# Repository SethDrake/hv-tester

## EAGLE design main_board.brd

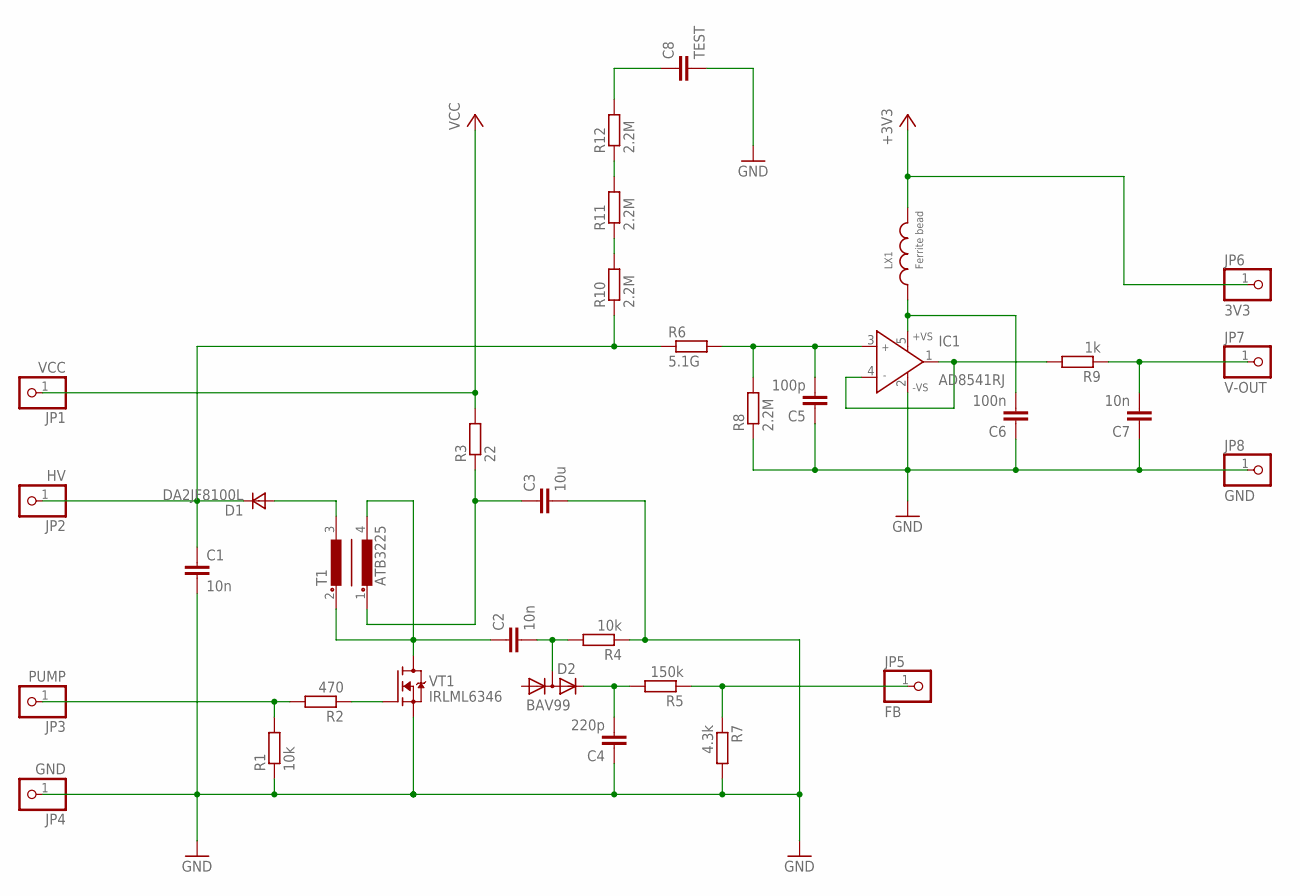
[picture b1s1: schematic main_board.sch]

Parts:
C1: 10n; C1206
C2, C7: 10n; C0805
C3: 10u; C0805
C4: 220p; C0805
C5: 100p; C0805
C6: 100n; C0805
C8: TEST; C1206
D1: DA2JF8100L; SOD323
D2: BAV99; SOT23
IC1: AD8541RJ; SOT23-5
JP1: VCC; 1X01
JP2: HV; 1X01
JP3: PUMP; 1X01
JP4, JP8: GND; 1X01
JP5: FB; 1X01
JP6: 3V3; 1X01
JP7: V-OUT; 1X01
LX1: Ferrite bead; WE-KI_0805A
R1, R4: 10k; M0805
R2: 470; M0805
R3: 22; M0805
R5: 150k; M0805
R6: 5.1G; P0817/22
R7: 4.3k; M0805
R8, R10, R11, R12: 2.2M; M0805
R9: 1k; M0805
T1: ATB3225
VT1: IRLML6346; SOT23

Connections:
+3V3: JP6.1, LX1.2
FB: JP5.1, R5.1, R7.1
GND: C1.2, C3.2, C4.1, C5.1, C6.1, C7.1, C8.2, IC1.2 (-VS), JP4.1, JP8.1, R1.1, R4.1, R7.2, R8.1, VT1.2 (S)
HV: C1.1, D1.1 (C), JP2.1, R6.1, R10.1
unnamed: D1.2 (A), T1.3
unnamed: C6.2, IC1.5 (+VS), LX1.1
unnamed: C2.1, T1.2, T1.4, VT1.3 (D)
unnamed: C3.1, R3.1, T1.1
unnamed: C2.2, D2.3 (K1A2), R4.2
unnamed: R10.2, R11.1
unnamed: R2.1, VT1.1 (G)
unnamed: R11.2, R12.1
unnamed: C4.2, D2.2 (K2), R5.2
unnamed: IC1.1 (OUT), IC1.4 (IN-), R9.2
unnamed: C5.2, IC1.3 (IN+), R6.2, R8.2
PUMP: JP3.1, R1.2, R2.2
TEST: C8.1, R12.2
V-OUT: C7.2, JP7.1, R9.1
VCC: JP1.1, R3.2

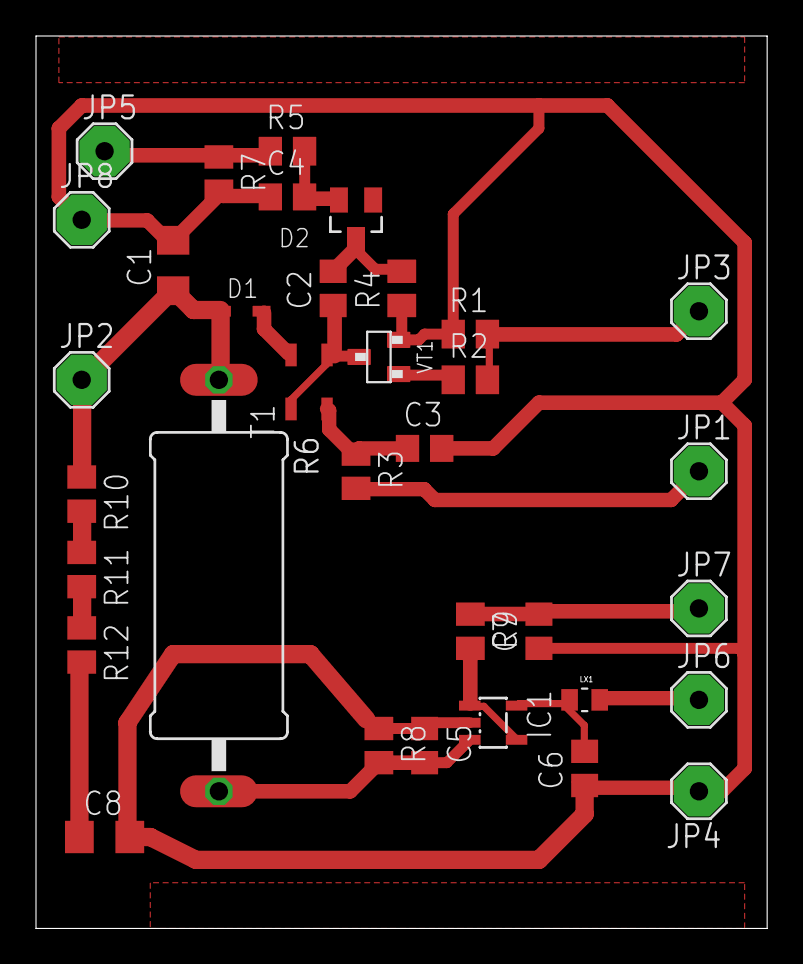
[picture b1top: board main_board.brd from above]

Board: 2 copper layers, 40.6 x 49.6 mm, 34 parts (0 on the bottom side), 19 nets.

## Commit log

2018-11-20 in progress..
2018-11-21 almost completed
2018-11-21 done
2018-11-30 fw started

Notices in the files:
parts and their libraries:
NXP_60_26022015: This library may be distributed and adapted freely for any purpose, as long as NXP is credited and any new creation is licensed under the same terms.
SignalCommunications: Copyright: Würth Elektronik
